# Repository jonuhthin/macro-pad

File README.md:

# macro-pad

Arduino Pro Micro HID device to act as a secondary keyboard for controlling volume and other functions, like a numpad

## Goals:

- use these components:
  - rotary encoder
  - cherry/kailh switches (I had browns laying around)
  - OLED screen
  - Arduino Pro Micro

nice to haves:

- be cheapish (< $50 USD)
- multiple layers of keybindings
- easy to customize mappings

## Implementation

- Custom PCB via KiCAD

  - You can safely ignore this, but you might notice there are a couple extra components on the PCB in the picture below. Those are for a 3 pin switch and an MCP73831 charging circuit. I included these for testing a charging circuit with a lithium ion cell and to potentially use the extra PCBs I received to make the whole thing wireless.

  ![[pcb-extra-components.png]]

- 3d modeled/printed housing and keycaps on Fusion 360
- QMK Firmware
  - I forked the QMK Firmware and created a layout for this keyboard
### BOM

_Disclaimer: I prorated the costs for these components. A lot of them are easier/cheaper to buy in multiples, but I use the components for other projects as well so I had a lot of them already (including a 3d printer). After shipping, I'm positive this was no longer <$50.00, so please see this more as a rough estimate of where the costs were for me._

| Part Description                                                                                                                                                                                                                                                                                                                                                                                                                                                                                                                                                                                                                                                                                                                                                                                                                                                                                                                                                                                                                                                                                                                                                                                                                             | Notes                                                                                                                                                                                                                          | Quantity | Total Price |
| -------------------------------------------------------------------------------------------------------------------------------------------------------------------------------------------------------------------------------------------------------------------------------------------------------------------------------------------------------------------------------------------------------------------------------------------------------------------------------------------------------------------------------------------------------------------------------------------------------------------------------------------------------------------------------------------------------------------------------------------------------------------------------------------------------------------------------------------------------------------------------------------------------------------------------------------------------------------------------------------------------------------------------------------------------------------------------------------------------------------------------------------------------------------------------------------------------------------------------------------- | ------------------------------------------------------------------------------------------------------------------------------------------------------------------------------------------------------------------------------ | -------- | ----------- |
| [Arduino Pro Micro](https://www.amazon.com/Teyleten-Robot-Bootloadered-Development-Microcontroller/dp/B08THVMQ46/ref=sr_1_1?crid=2VESLUXGU0N29&dib=eyJ2IjoiMSJ9.-hORpJsaUmiZ0DsxBhwltnZNUj96NW85UeZwIo4rCzSSD5IZJ2sQ8gR3akyhMcenOSP8NqMRcOHa2AP_5pMlEyGlhLkJ2gSFFIjhGe4lyhXQMHvHjqX4yFKkdq7h1H1a1aH4up-Rnf2nA0J-le_nhokiLFBPXCpjzcwTgPN8MOJMSTII0tUELs1rXE2TFy0hSmOPnfdzUMDdFU4aN-K7aQijzzNrcVrn42aWlh4boTbMW9m6hHN7ZdXmTZpA_cP4xhrr1GEdvoi87hhrpQQ1P_fH8KiM1B9NN2vwqEAYNq8.fBddrCWZP2I41st-l102FscxzcUn28_Y5U_SCSpWu38&dib_tag=se&keywords=pro+micro&qid=1722219576&s=electronics&sprefix=pro+micro%2Celectronics%2C85&sr=1-1 "https://www.amazon.com/Teyleten-Robot-Bootloadered-Development-Microcontroller/dp/B08THVMQ46/ref=sr_1_1?crid=2VESLUXGU0N29&dib=eyJ2IjoiMSJ9.-hORpJsaUmiZ0DsxBhwltnZNUj96NW85UeZwIo4rCzSSD5IZJ2sQ8gR3akyhMcenOSP8NqMRcOHa2AP_5pMlEyGlhLkJ2gSFFIjhGe4lyhXQMHvHjqX4yFKkdq7h1H1a1aH4up-Rnf2nA0J-le_nhokiLFBPXCpjzcwTgPN8MOJMSTII0tUELs1rXE2TFy0hSmOPnfdzUMDdFU4aN-K7aQijzzNrcVrn42aWlh4boTbMW9m6hHN7ZdXmTZpA_cP4xhrr1GEdvoi87hhrpQQ1P_fH8KiM1B9NN2vwqEAYNq8.fBddrCWZP2I41st-l102FscxzcUn28_Y5U_SCSpWu38&dib_tag=se&keywords=pro+micro&qid=1722219576&s=electronics&sprefix=pro+micro%2Celectronics%2C85&sr=1-1") | I used female pin headers to make the Pro Micro removable, if you don't use these you'll have to make adjustments to the model.                                                                                                | 1        | $6.29       |
| [Keyboard Switches](https://kbdfans.com/products/pls-do-not-delete-it-switch-option?_pos=7&_sid=81fc3dcd6&_ss=r&variant=39912664400011 "https://kbdfans.com/products/pls-do-not-delete-it-switch-option?_pos=7&_sid=81fc3dcd6&_ss=r&variant=39912664400011")                                                                                                                                                                                                                                                                                                                                                                                                                                                                                                                                                                                                                                                                                                                                                                                                                                                                                                                                                                                 | in my unprofessional opinion Gateron Yellows are the best value                                                                                                                                                                | 24       | $12.00      |
| [Rotary Encoder](https://www.amazon.com/Taiss-KY-040-Encoder-15%C3%9716-5-Arduino/dp/B07F26CT6B/ref=sr_1_2?dib=eyJ2IjoiMSJ9._s_FAhQr5PXlpTlOwNHvqxmNA_MXwOl_jKs_jX3zJP7OJPz78ybawFVX0qSHNl2IasIoPGXKgUDcxqB7WA0d5kgVVaADePFuRu5wHY0zLX0WsCfX_SuV0RAfCQ8t_e1JkH3_5Sdt8eAJ-80cS48xVpIyDNpS-LPlC3YPqvNwKxvV-GB5PRP7kqD1ljZPWhmqhTApwesUuD1jy6M_ZphAQhH6hq61gIClUBTqUBOLo1I._kYZ8rHNrynXbxVer7p3wGNRw9rx6ABgCqcK-rkMm4w&dib_tag=se&keywords=rotary+encoder&qid=1722470599&sr=8-2 "https://www.amazon.com/Taiss-KY-040-Encoder-15%C3%9716-5-Arduino/dp/B07F26CT6B/ref=sr_1_2?dib=eyJ2IjoiMSJ9._s_FAhQr5PXlpTlOwNHvqxmNA_MXwOl_jKs_jX3zJP7OJPz78ybawFVX0qSHNl2IasIoPGXKgUDcxqB7WA0d5kgVVaADePFuRu5wHY0zLX0WsCfX_SuV0RAfCQ8t_e1JkH3_5Sdt8eAJ-80cS48xVpIyDNpS-LPlC3YPqvNwKxvV-GB5PRP7kqD1ljZPWhmqhTApwesUuD1jy6M_ZphAQhH6hq61gIClUBTqUBOLo1I._kYZ8rHNrynXbxVer7p3wGNRw9rx6ABgCqcK-rkMm4w&dib_tag=se&keywords=rotary+encoder&qid=1722470599&sr=8-2")                                                                                                                                                                                                                                                                                                  | I had the kind linked with the breakout board, but if I had the chance I'd adjust the PCB to use one without a breakout like these [PEC12R](https://www.digikey.com/en/products/detail/bourns-inc/PEC12R-4225F-S0024/4499648)s | 1        | $2.00       |
| [SSD1306 OLED](https://www.amazon.com/Teyleten-Robot-Display-SSD1306-Raspberry/dp/B08ZY4YBHL/ref=sr_1_6?crid=1X1ODCPMBG4T7&dib=eyJ2IjoiMSJ9.l-FK2pxw8wWhZ_wtkFb4O317I1KcEin8dQMamdyEitE9LRh2ASA0jqjkAPis8a7H8O0BVjGwVcOVrv74dr2MPFvqay2peW42GiRTdbRF6hn0SXErhjwoKu8u_iuZIU4QpAGfImxPKWMZqECcr4cvEyHEu-duPwksqemCyrzq_fc-AOP-mXrxpfDBLmBpiCxFkXcxrjaRtNmS75Nmhz3cm8VC70wiUq7WHxFCZvfsyc4.O_p4mPadiFpwsO7idLw7kA7ve5s4o41nLcSCxjY9yI4&dib_tag=se&keywords=ssd1306+oled+display+module&qid=1722470662&sprefix=ssd1306%2Caps%2C91&sr=8-6 "https://www.amazon.com/Teyleten-Robot-Display-SSD1306-Raspberry/dp/B08ZY4YBHL/ref=sr_1_6?crid=1X1ODCPMBG4T7&dib=eyJ2IjoiMSJ9.l-FK2pxw8wWhZ_wtkFb4O317I1KcEin8dQMamdyEitE9LRh2ASA0jqjkAPis8a7H8O0BVjGwVcOVrv74dr2MPFvqay2peW42GiRTdbRF6hn0SXErhjwoKu8u_iuZIU4QpAGfImxPKWMZqECcr4cvEyHEu-duPwksqemCyrzq_fc-AOP-mXrxpfDBLmBpiCxFkXcxrjaRtNmS75Nmhz3cm8VC70wiUq7WHxFCZvfsyc4.O_p4mPadiFpwsO7idLw7kA7ve5s4o41nLcSCxjY9yI4&dib_tag=se&keywords=ssd1306+oled+display+module&qid=1722470662&sprefix=ssd1306%2Caps%2C91&sr=8-6")                                                                                                                                                                                |                                                                                                                                                                                                                                | 1        | $2.38       |
| PCB                                                                                                                                                                                                                                                                                                                                                                                                                                                                                                                                                                                                                                                                                                                                                                                                                                                                                                                                                                                                                                                                                                                                                                                                                                          | ordered from JLCPCB (upload Gerber.zip file)                                                                                                                                                                                   | 1        | $8.90       |
| LL4148 Diodes, JLCPCB #C435829                                                                                                                                                                                                                                                                                                                                                                                                                                                                                                                                                                                                                                                                                                                                                                                                                                                                                                                                                                                                                                                                                                                                                                                                               | If you don't do assembly through JLCPCB, you can order these separately on DigiKey or other electronics suppliers                                                                                                              | 24       | $1.87       |
| [M3 x 12mm](https://www.mcmaster.com/95263A146/ "https://www.mcmaster.com/95263A146/") SH                                                                                                                                                                                                                                                                                                                                                                                                                                                                                                                                                                                                                                                                                                                                                                                                                                                                                                                                                                                                                                                                                                                                                    |                                                                                                                                                                                                                                | 4        | $0.71       |
| PLA                                                                                                                                                                                                                                                                                                                                                                                                                                                                                                                                                                                                                                                                                                                                                                                                                                                                                                                                                                                                                                                                                                                                                                                                                                          |                                                                                                                                                                                                                                | ~100g    | $2.00       |
| **Total**                                                                                                                                                                                                                                                                                                                                                                                                                                                                                                                                                                                                                                                                                                                                                                                                                                                                                                                                                                                                                                                                                                                                                                                                                                    |                                                                                                                                                                                                                                |          | $36.15      |

## Build Instructions

1. Solder keycaps, OLED, rotary encoder, and headers to PCB.
1. Print 3d files:
	- [ ] 4 feet (foot.stl)
	- [ ] 1 base
	- [ ] 1 lid
	- [ ] 24 keycaps (or use real keycaps if you have them). I used kailh box switches, which required a slimmer stem, so you might be able to find a model (or generator: https://github.com/rsheldiii/KeyV2) with a stronger stem for regular switches.
1. Place PCB inside base. You may have to trim some of the pin headers down if there's some interference.
2. Place lid over
3. Secure together using M3 bolts screwed in from the bottom
4. Put keycaps/Pro Micro on
5. Program! 
	- you can use the firmware I put together [here](https://github.com/jonuhthin/qmk_firmware/tree/cf84ea766289dee4de3f93f87dd316478ff13fd7) , modifying keymap.c to your needs
	- follow QMK's documentation [here](https://docs.qmk.fm/newbs) if you decide to make this keyboard to set up your environment
	- run `make jonuhthin_24k_3dp:default` to build the .hex file
	- flash the .hex file to your Pro Micro using [QMK's toolbox](https://github.com/qmk/qmk_toolbox)

## Notes/Future Changes

Although I _probably_ won't iterate on this design further, here are some things I'd change if I did:

- [ ] space the mounting holes out by a few mm so they don't get close to the keys/other components
- [ ] move away from using a rotary encoder with a breakout board and just use one directly. The current way requires cutting the pin headers down to avoid interference
- [ ] reorient the screen or use a bigger (128x64) oled module
- [ ] add bluetooth support

Since this was a one-off project, I didn't worry much about the customization aspect (i.e. making the keymaps editable). If I get enough people interested, I'll submit the keymap to the QMK tool so everyone can edit keymaps more easily using the browser application.

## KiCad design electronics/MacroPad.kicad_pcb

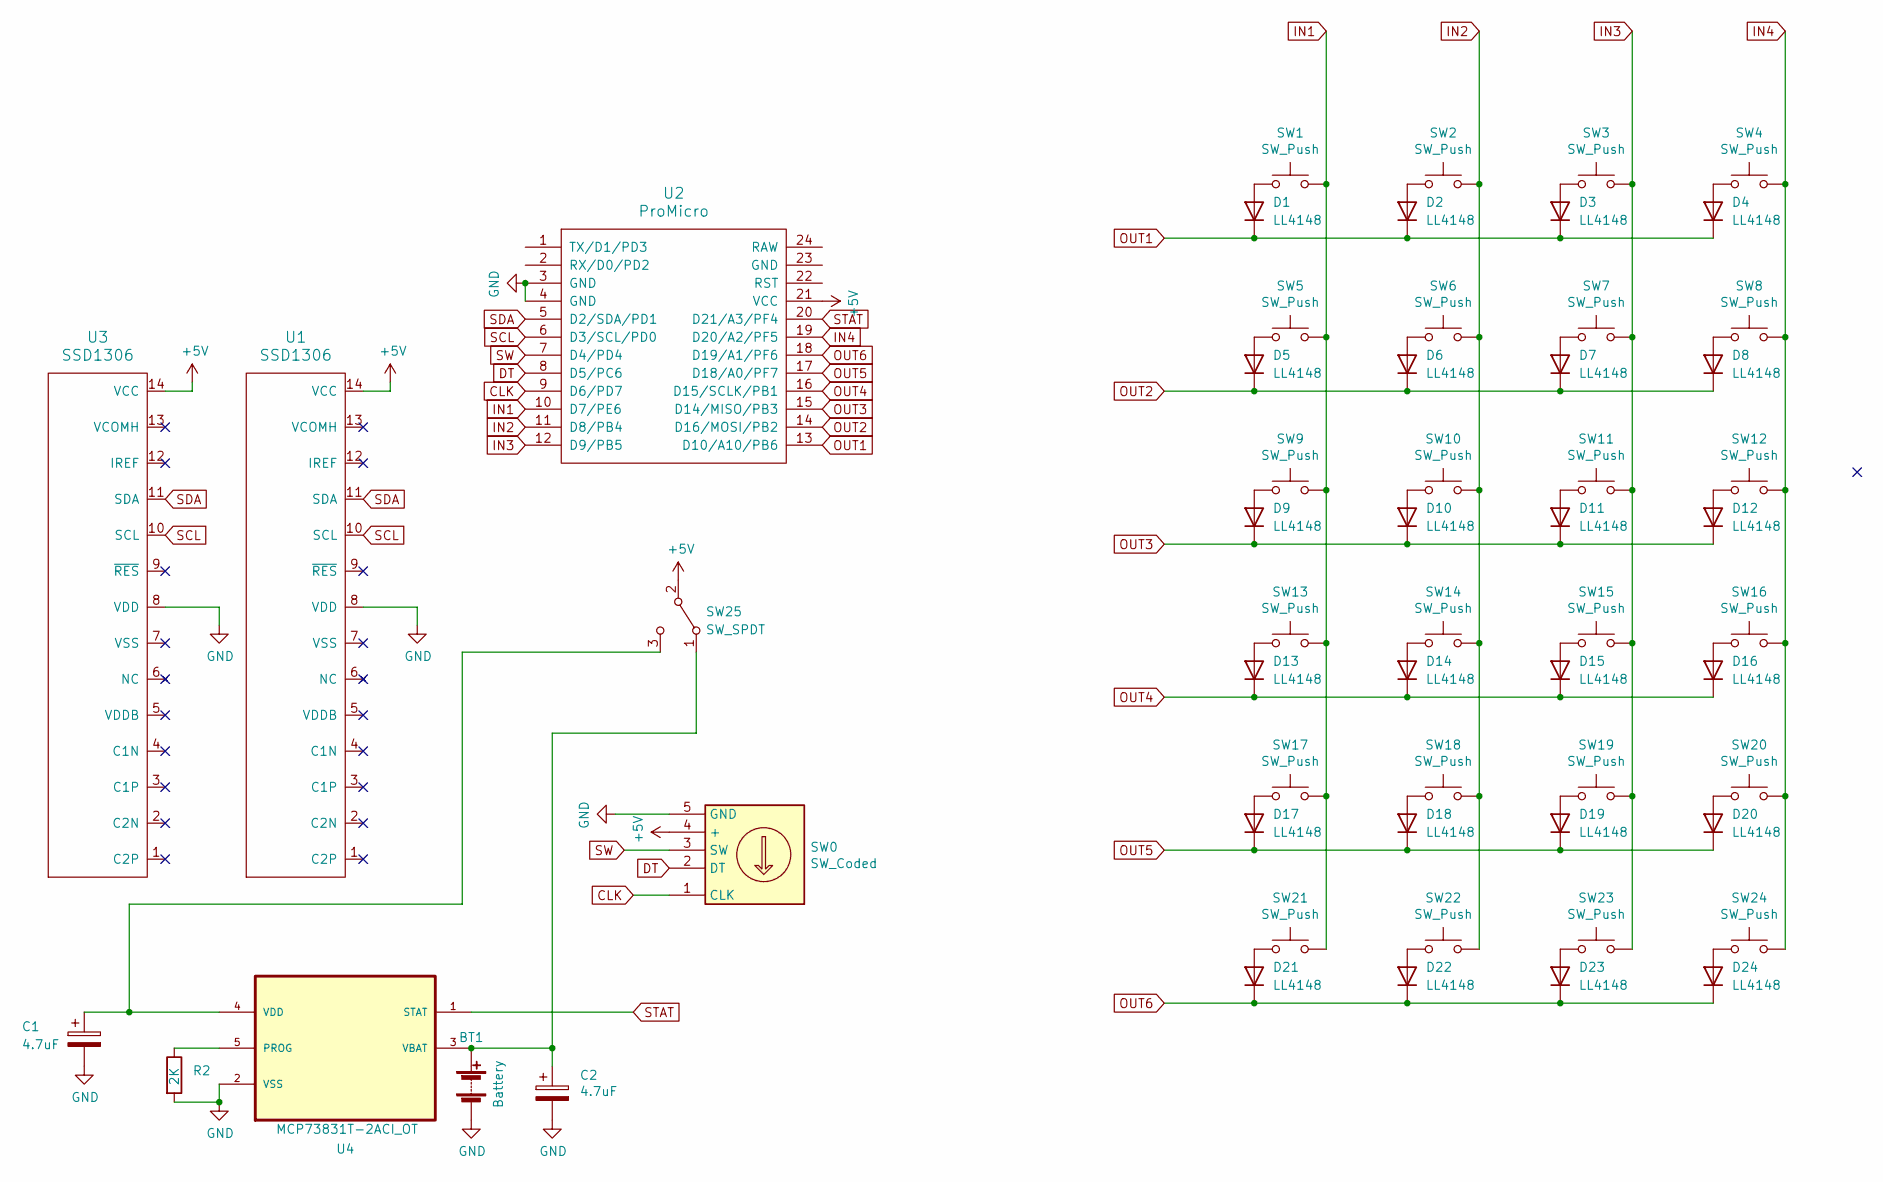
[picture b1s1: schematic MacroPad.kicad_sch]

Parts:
BT1: Battery; PinHeader_1x02_P2.00mm_Vertical
C1, C2: 4.7uF; C_0603_1608Metric_Pad1.08x0.95mm_HandSolder; LCSC C5252398
D1, D2, D3, D4, D5, D6, D7, D8, D9, D10, D11, D12, D13, D14, D15, D16, D17, D18, D19, D20, D21, D22, D23, D24: LL4148; LCSC C435829
R2: 2K; R_1210_3225Metric_Pad1.30x2.65mm_HandSolder; LCSC C137078
SW0: SW_Coded; PinHeader_1x05_P2.54mm_Vertical
SW1, SW2, SW3, SW4, SW5, SW6, SW7, SW8, SW9, SW10, SW11, SW12, SW13, SW14, SW15, SW16, SW17, SW18, SW19, SW20, SW21, SW22, SW23, SW24: SW_Push; SW_Cherry_MX_1.00u_PCB
SW25: SW_SPDT; PinHeader_1x03_P2.54mm_Vertical
U1, U3: SSD1306; SSD1306-0.91-OLED-4pin-128x32
U2: ProMicro; Sparkfun_Pro_Micro
U4: MCP73831T-2ACI_OT; SOT95P280X145-5N; MPN MCP73831T-2ACI/OT

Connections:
+5V: SW0.4 (+), SW25.2 (B), U1.14 (VCC), U2.21 (VCC), U3.14 (VCC)
CLK: SW0.1 (CLK), U2.9 (D6/PD7)
DT: SW0.2 (DT), U2.8 (D5/PC6)
GND: BT1.2 (-), C1.2, C2.2, R2.2, SW0.5 (GND), U1.8 (VDD), U2.3 (GND), U2.4 (GND), U3.8 (VDD), U4.2 (VSS)
IN1: SW1.2, SW5.2, SW9.2, SW13.2, SW17.2, SW21.2, U2.10 (D7/PE6)
IN2: SW2.2, SW6.2, SW10.2, SW14.2, SW18.2, SW22.2, U2.11 (D8/PB4)
IN3: SW3.2, SW7.2, SW11.2, SW15.2, SW19.2, SW23.2, U2.12 (D9/PB5)
IN4: SW4.2, SW8.2, SW12.2, SW16.2, SW20.2, SW24.2, U2.19 (D20/A2/PF5)
unnamed: BT1.1 (+), C2.1, SW25.1 (A), U4.3 (VBAT)
unnamed: D1.2 (A), SW1.1
unnamed: D2.2 (A), SW2.1
unnamed: D3.2 (A), SW3.1
unnamed: D4.2 (A), SW4.1
unnamed: D5.2 (A), SW5.1
unnamed: D6.2 (A), SW6.1
unnamed: D7.2 (A), SW7.1
unnamed: D8.2 (A), SW8.1
unnamed: D9.2 (A), SW9.1
unnamed: D10.2 (A), SW10.1
unnamed: D11.2 (A), SW11.1
unnamed: D12.2 (A), SW12.1
unnamed: D13.2 (A), SW13.1
unnamed: D14.2 (A), SW14.1
unnamed: D15.2 (A), SW15.1
unnamed: D16.2 (A), SW16.1
unnamed: D17.2 (A), SW17.1
unnamed: D18.2 (A), SW18.1
unnamed: D19.2 (A), SW19.1
unnamed: D20.2 (A), SW20.1
unnamed: D21.2 (A), SW21.1
unnamed: D22.2 (A), SW22.1
unnamed: D23.2 (A), SW23.1
unnamed: D24.2 (A), SW24.1
unnamed: C1.1, SW25.3 (C), U4.4 (VDD)
unnamed: R2.1, U4.5 (PROG)
OUT1: D1.1 (K), D2.1 (K), D3.1 (K), D4.1 (K), U2.13 (D10/A10/PB6)
OUT2: D5.1 (K), D6.1 (K), D7.1 (K), D8.1 (K), U2.14 (D16/MOSI/PB2)
OUT3: D9.1 (K), D10.1 (K), D11.1 (K), D12.1 (K), U2.15 (D14/MISO/PB3)
OUT4: D13.1 (K), D14.1 (K), D15.1 (K), D16.1 (K), U2.16 (D15/SCLK/PB1)
OUT5: D17.1 (K), D18.1 (K), D19.1 (K), D20.1 (K), U2.17 (D18/A0/PF7)
OUT6: D21.1 (K), D22.1 (K), D23.1 (K), D24.1 (K), U2.18 (D19/A1/PF6)
SCL: U1.10 (SCL), U2.6 (D3/SCL/PD0), U3.10 (SCL)
SDA: U1.11 (SDA), U2.5 (D2/SDA/PD1), U3.11 (SDA)
STAT: U2.20 (D21/A3/PF4), U4.1 (STAT)
SW: SW0.3 (SW), U2.7 (D4/PD4)

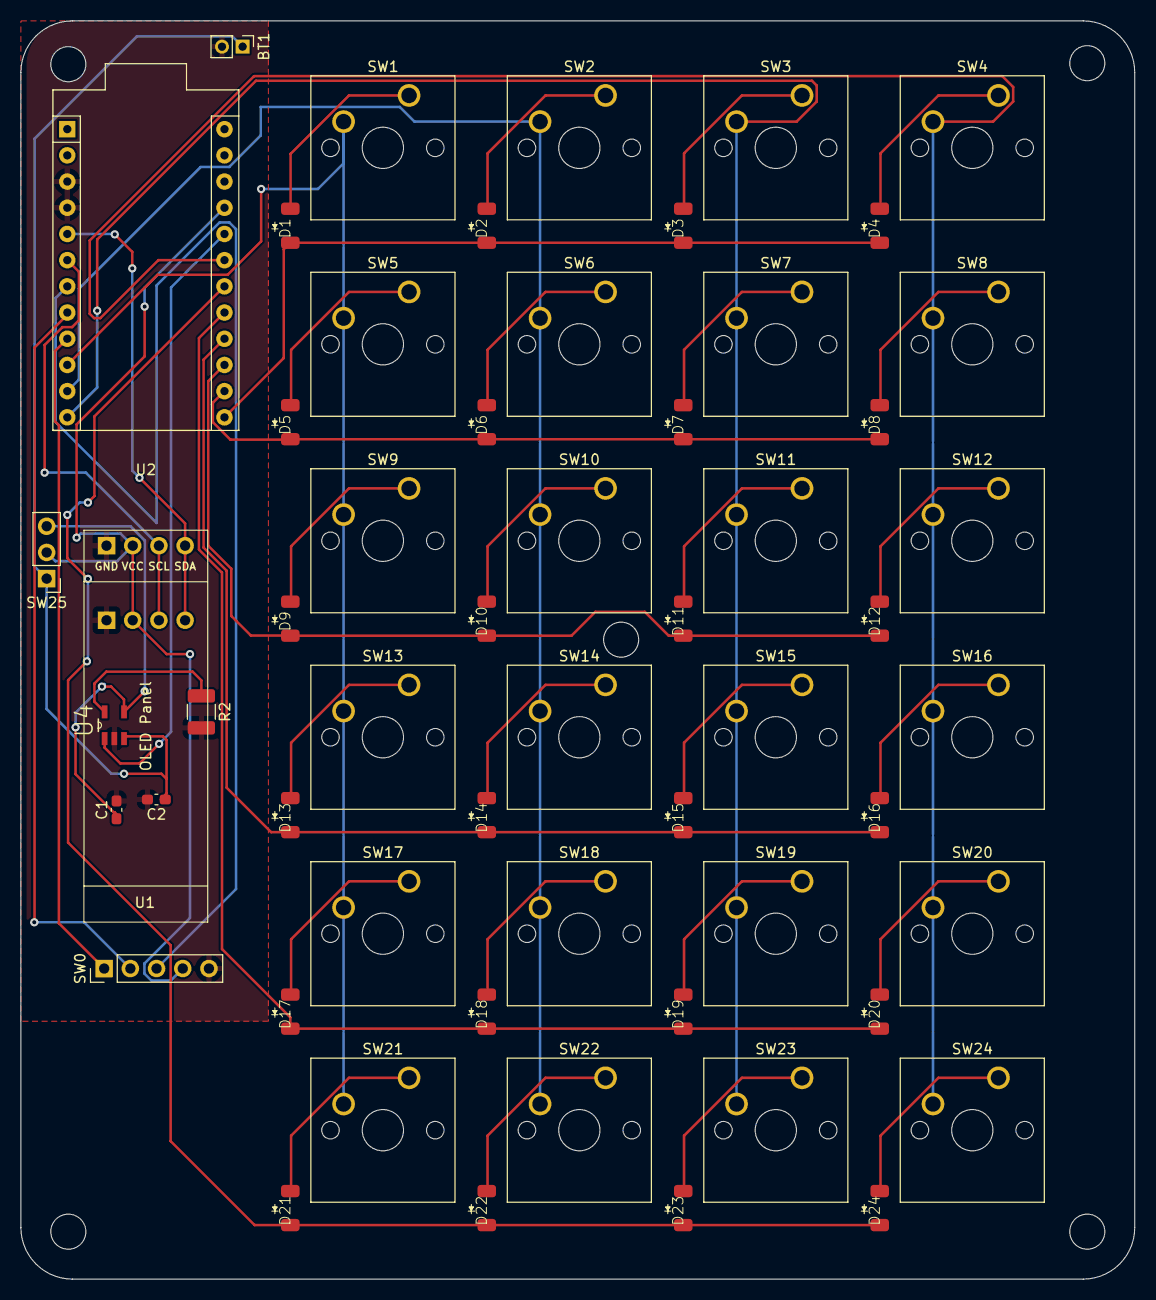
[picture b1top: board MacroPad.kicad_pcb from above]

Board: 2 copper layers, 108.0 x 122.0 mm, 58 parts (1 on the bottom side), 45 nets.

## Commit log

2024-06-19 cleaned for v2
2024-07-21 platformio conversion
2024-07-21 cleaning
2024-07-21 patch to Keypad lib
2024-07-22 add fusion file
2024-07-25 add qmk config
2024-07-25 rotary encoder support
2024-08-01 update docs
2024-08-01 rm platformio scripts
2024-08-02 generalize web link
2024-08-04 clean docs
